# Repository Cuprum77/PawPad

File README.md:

# PawPad
## PawPad programming header
This is a project that aims to spice up the world of boring test jigs and programming headers with a completely new, full stack system for adding programming headers to your boards.
<div>

</div>

## Why should I use this?

There are many benefits in the above shape compared to regular arrangements:
* No acid traps due to smooth curves
* No holes in the PCB means easier routing
* Big enough to solder wires to when needed, yet compact enough to be practical
* Large surface area makes it hard to peel the pads off and easier to hit with a jig
* Pretty
## Files
[PawPad](../main/PawPad) - contains the KiCAD footprint.

[Programming Jig](<../main/Programming Jig>) - contains a programming jig meant to be screwed onto a piece of 10x10 aluminium extrusion/makerbeam.
<div>

</div>
NOTE: this jig is not complete! It has not yet been tested for actual programming and may not be ideal!

## Pinout
The pinout is standardized as outlined below:

Pin | SWD | JTAG | SPI / ICSP | UART | I2C
:---: | :---: | :---: | :---: | :---: | :---:
Bean (1) | SWO | TDO | MISO | RX | -
Bean (2) | SWDIO | TDI | MOSI | TX | SDA
Bean (3) | SWCLK | TCK | SCK | - | SCL
Bean (4) | NRST | TMS | RST | RST | RST
Big Bean (5) | GND | GND | GND | GND | GND

<div>

</div>

## Showcase
Did you add this to your PCBs? Let us know by opening an [Issue](https://github.com/Cuprum77/PawPad/issues/new)!

Example of the [Programming Jig](<../main/Programming Jig>) in action on a test PCB:
<div>

</div>

## Future plans
* Alternative designs with different numbers of pins
* Unified pinout standard
* OSHW certification
* Debugger design

### Acknowlegments
This has been inspired by the [original maker of the footprint](https://github.com/the6p4c/pawpad), go check them out.

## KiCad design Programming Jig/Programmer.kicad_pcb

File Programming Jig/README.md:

# PawPad Programming Jig
This is an experimental programming jig for PawPad. It still requires real world testing, but continuity tests have proven the design to be sound.

## Use case
This jig is meant to fan out the PawPad connector to the common SWD and ICSP connectors. 
Please do not try to connect them together or plug in other programmers than what you intend to use, as there is no protection circuitry on this!

## How to assemble
Soldering the jig is difficult, it is recommended that you order or get more than a single PCB made. That way you can screw them together and use the holes to keep the pogo pins straight. 

However, due to the size, it should be noted that they might be hard to solder by hand, and might require some fiddling get it to work.

## Future plans
* Add a 3D printable jig to hold the pogo pins in place
* Create a cheaper mounting solution

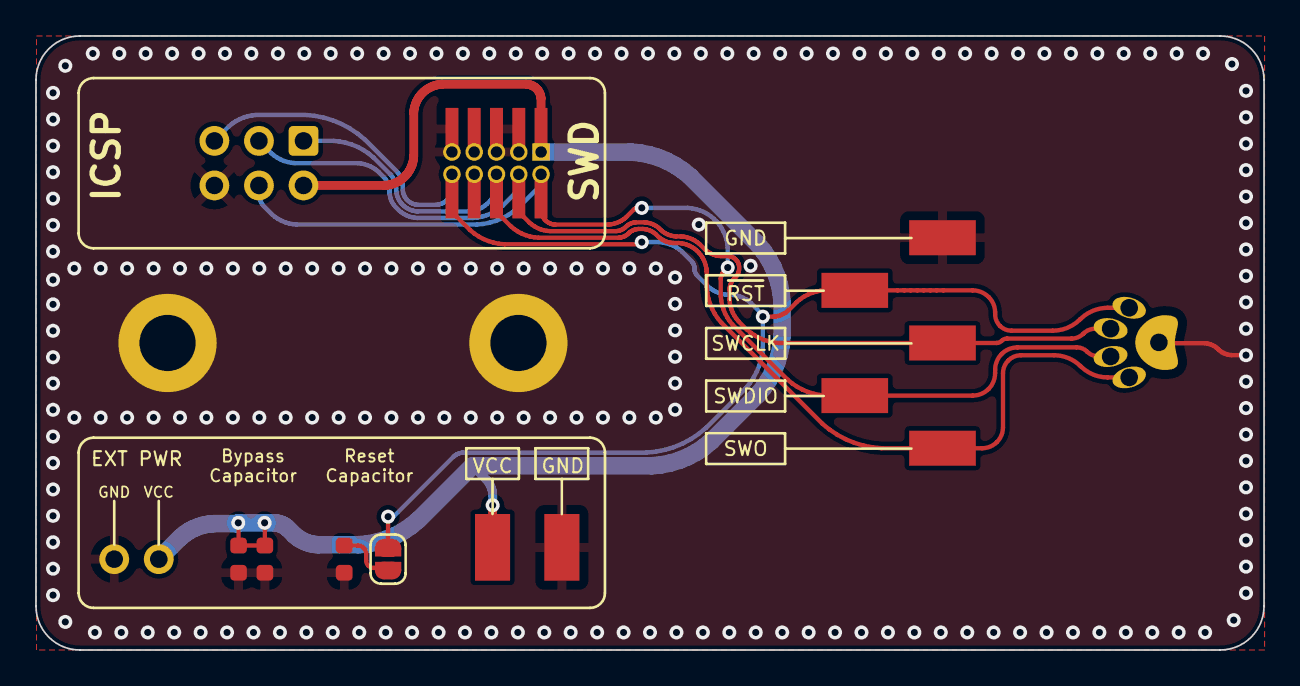
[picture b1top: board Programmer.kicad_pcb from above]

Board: 2 copper layers, 70.0 x 35.0 mm, 18 parts (0 on the bottom side), 9 nets.

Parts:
C1, C2: 100n; C_0603_1608Metric
C3: 100p; C_0603_1608Metric
H1, H2: M3; MountingHole_3.2mm_M3_DIN965_Pad
J1: ICSP; IDC-Header_2x03_P2.54mm_Vertical
J2: PawPrint; pawpad_holeless
J3: PM20B05VBDN; PinHeader_2x05_P1.27mm_Vertical_SMD
J4: THT variant; PinHeader_2x05_P1.27mm_Vertical
J5: Power; PinSocket_1x02_P2.54mm_Vertical
JP1: RST Capacitor; SolderJumper-2_P1.3mm_Open_RoundedPad1.0x1.5mm
TP1, TP2, TP3, TP4, TP5: TestPoint; TestPoint_Keystone_5019_Minature_No_Silkscreen
TP6: 1; TestPoint_Keystone_5019_Minature_No_Silkscreen
TP7: 2; TestPoint_Keystone_5019_Minature_No_Silkscreen

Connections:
/NRST/RST: J1.5, J2.4, J3.10, J4.10, JP1.1 (A), TP5.1
/N/A_L: J3.7, J4.7
/N/A_R: J3.8, J4.8
/SWCLK/SCK: J1.3, J2.3, J3.4, J4.4, TP4.1
/SWDIO/MOSI: J1.4, J2.2, J3.2, J4.2, TP3.1
/SWO/MISO: J1.1, J2.1, J3.6, J4.6, TP1.1
GND: C1.2, C2.2, C3.2, H1.1, H2.1, J1.6, J2.5, J3.3, J3.5, J3.9, J4.3, J4.5, J4.9, J5.2, TP2.1, TP7.1
unnamed: C1.1, JP1.2 (B)
VCC: C2.1, C3.1, J1.2, J3.1, J4.1, J5.1, TP6.1

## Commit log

2023-03-08 added pawpad and programmming jig
2023-03-08 images of programmer
2023-03-08 added pinout and irl example
2023-03-08 spelling mistake
2023-03-08 added pinout diagram
2023-03-08 readme for programming jig
2023-03-08 added symbols
2023-03-08 restructure
2023-03-09 loicense
2023-03-09 Development (#1)
    * added symbols
    * restructure
    * loicense
